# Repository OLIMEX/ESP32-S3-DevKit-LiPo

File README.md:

# ESP32-S3-DevKit-LiPo
ESP32-S3 development board with JTAG/USB-OTG and LiPo charger

ESP32-S3-DevKit-LiPo is small board capable to run Linux kernel 6.3

## Features

* ESP32-S3-WROOM-1-N8R8 8MB RAM 8 MB Flash
* Green Status LED
* Yellow Charge LED
* pUEXT connector
* USB-C power supply and USB-Serial programmer
* USB-C OTG JTAG/Serial connector
* LiPo charger
* LiPo battery connector
* External power sense
* Battery measurement
* Automatic power supply switch between USB and LiPo
* RESET button
* USER button

## Licenses

* Hardware is released under CERN Open Hardware Licence Version 2 - Strongly Reciprocal, all silkscreen credits to Olimex should remain;
* Software is released under GPL3 Licensee
* Documentation is released under CC BY-SA 3.0

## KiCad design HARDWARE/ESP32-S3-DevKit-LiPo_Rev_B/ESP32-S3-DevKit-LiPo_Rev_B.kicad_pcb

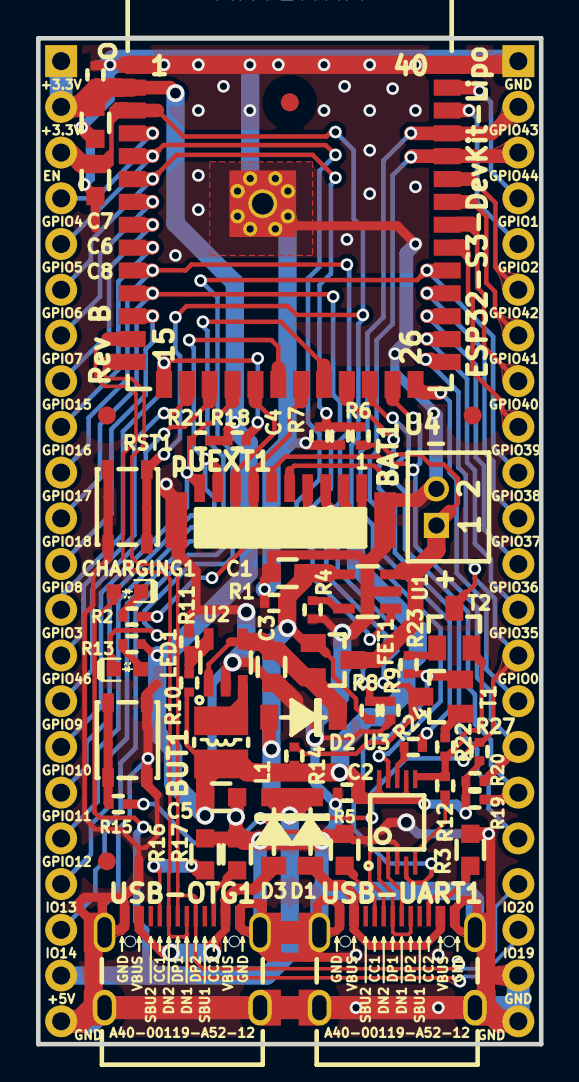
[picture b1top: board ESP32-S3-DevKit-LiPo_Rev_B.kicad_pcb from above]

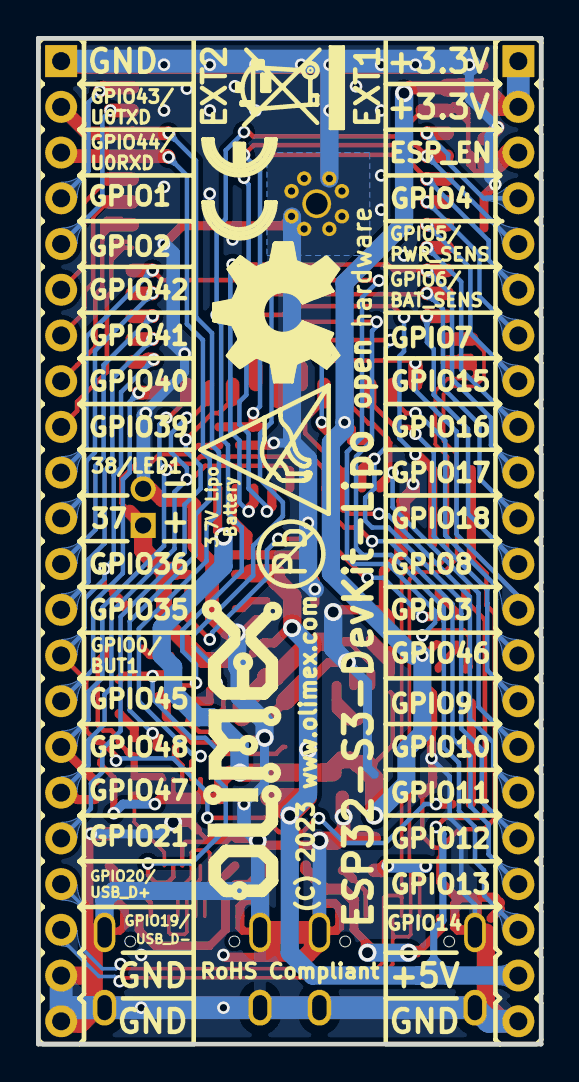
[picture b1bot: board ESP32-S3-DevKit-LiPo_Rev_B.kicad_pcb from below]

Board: 2 copper layers, 27.9 x 55.9 mm, 64 parts (8 on the bottom side), 63 nets.

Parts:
BAT1: DW02S; LIPO_BAT_VERTICAL_DW02S
BUT1: YTS-A016-X
C1, C3, C5, C6: 22uF/6.3V/20%/X5R/C0603; C_0603_5MIL_DWS
C2, C4, C7: 100nF/10V/10%/X7R/C0402; C_0402_5MIL_DWS
C8: 1uF/10V/10%/X5R/C0603; C_0603_5MIL_DWS
CHARGING1: LED/YELLOW/0603; LED_0603_KA
D1, D2, D3: 1N5819S4/SOD123; SOD-123_1C-2A_KA
EXT1, EXT2: HN1x22
FET1: WPM2015-3/TR; SOT23
FID1, FID2, FID3, FID4: Fiducial; Fiducial1x3
L1: 2.2uH/1.5A/DCR=72mR/20%/3.00x3.00x1.50mm/CD32(NR3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; CD32
LED1: LED/Green/0603; LED_0603_KA
Logo_OLIMEX_TB: Logo_OLIMEX_TB
R1, R4, R14, R18, R21: 10k/R0402; R_0402_5MIL_DWS
R2, R13, R19, R20: 2.2k/R0402; R_0402_5MIL_DWS
R3, R5, R16, R17: 5.1k/R0603; R_0603_5MIL_DWS
R6, R9: 470k/R0402; R_0402_5MIL_DWS
R7: 150k/R0402; R_0402_5MIL_DWS
R8, R10: 220k/R0402; R_0402_5MIL_DWS
R11: 49.9k/1%/R0402; R_0402_5MIL_DWS
R12: 4.7k/R0402; R_0402_5MIL_DWS
R15, R24: 100R/R0402; R_0402_5MIL_DWS
R22, R23: 1k/R0402; R_0402_5MIL_DWS
R27: NA/R0402; R_0402_5MIL_DWS
RST1: YTS-A016-X
Sign_Antistatic: Sign_Antistatic
Sign_CE: CE_Sign
Sign_OSHW_8x8: Sign_OSHW_8x8
Sign_PB-Free: Sign_PB-Free
Sign_RecycleBin_1: Sign_RecycleBin_1
T1, T2: BC817-40(SOT23); SOT23
U1: BL4054B-42TPRN(SOT23-5); SOT-23-5
U2: SY8089AAAC(SOT23-5); SOT-23-5
U3: CH340X(MSOP-10); MSOP-10_Pitch-0.5mm_3.00x3.00x1.00mm
U4: ESP32-S3-WROOM-1-N8R8; ESP32-­S3-­WROOM­-1
USB-OTG1: USB-C-16P-F(A40-00119-A52-12); USB2.0_TYPE-C(A40-00119-A52-12)
USB-UART1: USB-C-16P-F(A40-00119-A52-12); USB2.0_TYPE-C(A40-00119-A52-12)
pUEXT1: JST_BM10B-SRSS-TB; BM10B-SRSS-TB

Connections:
+3.3V: C2.1, C5.1, C6.1, C7.2, EXT1.1, EXT1.2, L1.2, R10.2, R13.1, R14.1, R18.1, R19.1, R20.1, R21.1, R27.1, U3.7, U3.10, U4.2, pUEXT1.1
+5V: C1.1, CHARGING1.2, D1.1, D2.2, D3.1, EXT1.21, FET1.1, R1.1, R8.1, U1.4
/ESP_EN: C8.1, EXT1.3, R14.2, RST1.2, T1.3, U4.3
/GPIO0\BUT1: EXT2.14, R15.1, R27.2, T2.3, U4.27
/GPIO1: EXT2.4, U4.39
/GPIO2: EXT2.5, U4.38
/GPIO3: EXT1.13, R18.2, U4.15
/GPIO4: EXT1.4, U4.4
/GPIO5\PWR_SENS: EXT1.5, R8.2, R9.1, U4.5
/GPIO6\BAT_SENS: C4.2, EXT1.6, R6.2, R7.1, U4.6
/GPIO7: EXT1.7, U4.7
/GPIO8: EXT1.12, U4.12
/GPIO9: EXT1.15, U4.17
/GPIO10\FSPICS0(SPI3_CS0): EXT1.16, R21.2, U4.18, pUEXT1.10
/GPIO11\FSPID(SPI3_MOSI): EXT1.17, U4.19, pUEXT1.8
/GPIO12\FSPICLK(SPI3_CLK): EXT1.18, U4.20, pUEXT1.9
/GPIO13\FSPIQ(SPI3_MISO): EXT1.19, U4.21, pUEXT1.7
/GPIO14: EXT1.20, U4.22
/GPIO15: EXT1.8, U4.8
/GPIO16: EXT1.9, U4.9
/GPIO17\U1TXD: EXT1.10, U4.10, pUEXT1.3
/GPIO18\U1RXD: EXT1.11, U4.11, pUEXT1.4
/GPIO19\USB_D-: EXT2.20, U4.13, USB-OTG1.A7, USB-OTG1.B7
/GPIO20\USB_D+: EXT2.19, U4.14, USB-OTG1.A6, USB-OTG1.B6
/GPIO21: EXT2.18, U4.23
/GPIO35: EXT2.13, U4.28
/GPIO36: EXT2.12, U4.29
/GPIO37: EXT2.11, U4.30
/GPIO38\LED1: EXT2.10, LED1.1, U4.31
/GPIO39: EXT2.9, U4.32
/GPIO40: EXT2.8, U4.33
/GPIO41: EXT2.7, U4.34
/GPIO42: EXT2.6, U4.35
/GPIO43\U0TXD: EXT2.2, U3.9, U4.37
/GPIO44\U0RXD: EXT2.3, R24.2, U4.36
/GPIO45: EXT2.15, U4.26
/GPIO46: EXT1.14, U4.16
/GPIO47\I2C_SCL: EXT2.17, R19.2, U4.24, pUEXT1.5
/GPIO48\I2C_SDA: EXT2.16, R20.2, U4.25, pUEXT1.6
/UD+: U3.1, USB-UART1.A6, USB-UART1.B6
/UD-: U3.2, USB-UART1.A7, USB-UART1.B7
GND: BAT1.2, BUT1.2, C1.2, C2.2, C3.2, C4.1, C5.2, C6.2, C7.1, C8.2, EXT1.22, EXT2.1, EXT2.21, EXT2.22, R1.2, R3.1, R4.2, R5.1, R7.2, R9.2, R11.2, R16.1, R17.1, RST1.1, U1.2, U2.2, U3.3, U4.1, U4.40, U4.41, USB-OTG1.0, USB-OTG1.A1, USB-OTG1.A12, USB-OTG1.B1, USB-OTG1.B12, USB-UART1.0, USB-UART1.A1, USB-UART1.A12, USB-UART1.B1, USB-UART1.B12, pUEXT1.0, pUEXT1.2
unnamed: BUT1.1, R15.2
unnamed: C3.1, D2.1, FET1.2, U2.1, U2.4
unnamed: CHARGING1.1, R2.1
unnamed: D1.2, USB-UART1.A4, USB-UART1.A9, USB-UART1.B4, USB-UART1.B9
unnamed: D3.2, USB-OTG1.A4, USB-OTG1.A9, USB-OTG1.B4, USB-OTG1.B9
unnamed: L1.1, U2.3
unnamed: LED1.2, R13.2
unnamed: R2.2, U1.1
unnamed: R3.2, USB-UART1.B5
unnamed: R4.1, U1.5
unnamed: R5.2, USB-UART1.A5
unnamed: R10.1, R11.1, U2.5
unnamed: R12.1, U3.5
unnamed: R12.2, R22.1, T2.2, U3.6
unnamed: R16.2, USB-OTG1.A5
unnamed: R17.2, USB-OTG1.B5
unnamed: R22.2, T1.1
unnamed: R23.1, T1.2, U3.4
unnamed: R23.2, T2.1
unnamed: R24.1, U3.8
VBAT: BAT1.1, FET1.3, R6.1, U1.3

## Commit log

2023-07-28 initial upload
2024-07-05 Update
    Diemsnions
2026-02-17 New demo
    Arduino demo for battery sense and battery measurement
2026-02-24 Update
    New demo and fixed Arduino settings to fit the PSRAM type
2026-03-06 Update
    added json and yaml for platformio and esphome
2026-06-15 Update
    Motion detection

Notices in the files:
HARDWARE/ESP32-S3-DevKit-LiPo_Rev_B/ESP32-S3-DevKit-LiPo_Rev_B.kicad_pcb:
(C) 2023
